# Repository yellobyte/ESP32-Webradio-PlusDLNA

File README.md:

# ESP32 Webradio++

This ESP32 internet radio implementation is partially based on Ed Smallenburgs (ed@smallenburg.nl) original ESP32 Radio project, version 10.06.2018. His active & very popular web radio project is documented [here](https://github.com/Edzelf/ESP32-radio).  

It all started when my much loved 1991's FM Tuner device **TECHNICS Tuner ST-G570** became obsolete and useless (at least for me). I simply couldn't listen to my favourite FM radio stations anymore after having moved abroad. Since I didn't want to part with the old longtime pal, the decision was made to give it a second life: housing a modern internet radio with lots of additional features.  

Now, after putting countless hours into the project, the device not only plays **internet radio streams** and audio files from **SD cards** but also **audio content from DLNA media servers** in the same LAN.  

The Arduino library **SoapESP32** has been created especially for the latter feature and enables any ESP32 based device to connect to DLNA media servers in the local network, browse their content and download selected files. It is basically a byproduct of this project and is now listed in the official Arduino library [collection](https://www.arduino.cc/reference/en/libraries/category/communication/).  

## :gift: Feature list:

Starting from Ed Smallenburg's code (Version 10.06.2018) this project has seen a lot of additions and modifications over time. Here a summary:

 * Integration of [SoapESP32](https://github.com/yellobyte/SoapESP32) library for DLNA media server access
 * Digital audio output added (TOSLINK optical) using a WM8805 module from Aliexpress
 * Usage of special VS1053 decoder board (with I2S output and without 3.5mm audio socket)<br />
   -> You find the Eagle schematic & board files [here](https://github.com/yellobyte/ESP32-Webradio-PlusDLNA/tree/main/EagleFiles).
 * VS1053 gets patched with new firmware v2.7 at each reboot<br />
   -> Latest firmware patches for the VLSI VS1053 are available from [here](http://www.vlsi.fi/en/support/software/vs10xxpatches.html).
 * VU meter added to TFT display (needs above mentioned firmware patch)
 * Usage of W5500 Ethernet module instead of ESP32 builtin WiFi
 * Option to use a Debug Server on port 23 for debug output (in this case the cmd server is disabled due to Ethernet socket shortage)
 * Handling of the original front panel buttons & LEDs with the aid of an extender module (connected to ESP32 via I2C)
 * SD card indexing code rewritten in large parts
 * Ability to update ESP32 Radio code via SD card (using OTA functionality during reboot)
 * New rotary encoder fitted to available rotary knob, debouncing done in hardware
 * Track progress bar while playing audio files from SD card or media server
 * Minor modifications to get an unspecified Ali 21-button remote control working
 * MQTT functionality & battery stuff removed completely
 * Handling of more special chars in webradio streams (some radio channels seem to have different utf8 conversion tables)
 * Quicker handling of (very rare) firmware crashes resulting in shorter recovery/reboot time
 * Countless minor changes, adjustments, bugfixing
 * Regular modifications if required for building with new espressif32 framework releases   

If interested, have a look at [Revision history.txt](https://github.com/yellobyte/ESP32-Webradio-PlusDLNA/blob/main/Doc/Revision%20history.txt) in the doc folder. 

## Some technical details:
The original display (rendered useless) has been removed and it's plexiglass cover now hides the infrared sensor VS1838B which receives signals from a remote control. A small 1.8" TFT color display (160x128 pixel, ST7735 driver IC, PCI bus) has been added to the front and is used for interacting with the user and presenting essential info. The necessary cutout in the front has been made with a small and affordable Proxxon mill/drill unit used by many hobbyists. A thin plexiglass is glued into the cutout. The TFT display sits right behind it, mounted on a frame made from PCB material to keep it in place. 

After milling/drilling the front was thoroughly cleaned to get a smooth surface and then the upper flat part of it was painted black twice with a bottle of color spray. It rested 3 days in the sun to dry completely before being reattached to the case. A silver permanent marker was used to label the buttons later on.  

The original encoder attached to the rotary knob has been replaced with a modern one (Stec Rotary Encoder STEC11B03, 1 impulse per 2 clicks, turn + push). The knob is now used to browse through the list of pre-configured web radio stations, the content of SD cards or DLNA media servers storing thousands of audio files. Going up and down the directory levels and finally selecting an audio file for playing is done very fast with the knob in combination with the small 'return' button next to it.  

Most of the original front buttons are still available and used for changing modes (Radio, SD card or DLNA), skipping tracks and selecting a repeat mode (None, Track, List or Random). Two adjacent buttons just below the TFT display went into the bin and made room for a SD card module (PCI bus with 4MHz clock speed only for stability reasons).   

A special extender board connects the mainboard with the original front PCB. This board makes it possible to control LEDs and buttons via the original control matrix. The existing 10 channel buttons (1...8,9,0) can continue to serve their original purpose, only this time with web radio stations assigned. The infrared sensor is attached to the extender board as well. 

The extender board contains two 'Remote 8-Bit I/O Expander for I2C Bus ICs' PCF8574 and is connected to the mainboard via I2C bus. Its only task is to provide additional IO ports to the ESP32 on the mainboard. Jumper JP1 on the board is open as the interrupt signal INT from both ICs is unused. Every ~60ms the ICs get polled from the ESP32 instead.

The original front panel 7x4 control matrix has all buttons connected between 7 rows and 4 columns as shown below. Quite a few single header pins had to be soldered onto the front panel PCB to get electrical access to the matrix. 

Rows 1...7 of the matrix (from top to bottom) are wired to connectors SV1 and SV2 on the extender board as follows:  
 * Row 1 (CP103/5) --> SV1/5 (PCF8574-1/P4, output)
 * Row 2 (CP103/4) is unused (buttons 'Preset up/down' have been removed)
 * Row 3 (CP102/8) --> SV2/2 (PCF8574-2/P1, output)
 * Row 4 (CP102/9) --> SV2/1 (PCF8574-2/P0, output)
 * Row 5 (CP103/6) --> SV1/6 (PCF8574-1/P5, output)
 * Row 6 (CP103/7) --> SV1/7 (PCF8574-1/P6, output)
 * Row 7 (CP103/8) --> SV1/8 (PCF8574-1/P7, output)

And colums 1...4 (from left to right) are wired to the extender board as follows:  
 * Column 1 (CP103/1) --> SV1/1 (PCF8574-1/P0, input, with 8.2k pull-up resistor to 3V3)
 * Column 2 (CP103/2) --> SV1/2 (PCF8574-1/P1, input, with 8.2k pull-up resistor to 3V3)
 * Column 3 (CP103/3) --> SV1/3 (PCF8574-1/P2, input, with 8.2k pull-up resistor to 3V3)
 * Column 4 (CP102/7) --> SV1/4 (PCF8574-1/P3, input, with 8.2k pull-up resistor to 3V3)

In order to detect pressed buttons the extender board successively pulls the rows LOW and checks it's column input lines for a HIGH to LOW transition because any button pressed will then subsequently pull its corresponding column to LOW as well.

The extender board additionally drives the 3 front panel LEDs via IC PCF8574-2/P5-P7 (connector pins SV2/6...8) by setting the lines to LOW. Those 3 lines plus 3V3 are wired directly to a separate LED PCB next to the rotary encoder.  

As for now, the device consists of several separate modules/PCBs. Three modules (ESP32, TOSLINK optical output, 10/100Mb Ethernet) were bought from various internet shops and the other four modules (power supply, mainboard, VS1053B decoder and front extender) were especially designed for this project with EAGLE PCB Design & Layout tool. The PCBs were ordered unassembled from various PCB prototype manufacturers in CN for little money. I did all the soldering myself, the decoder chip VS1053B in a tiny LQFP-48 package was a challenge though. All relevant EAGLE project files, schematics, board layouts etc. are available [here](https://github.com/yellobyte/ESP32-Webradio-PlusDLNA/tree/main/EagleFiles).  

The analog audio output socket, the power input socket, the common mode choke and the many PCB distance holders were harvested from the original tuner PCBs and reused. Their Eagle-Libraries are located [here](https://github.com/yellobyte/Eagle-Component-Library). The mounting holes on the new PCBs were placed in a way to match the existing mounting holes at the bottom of the case.  

A necessary audio amplifier can be connected via the analog audio output or even the TOSLINK optical output for better sound quality. Well, going digital at the output is probably useless for web radio stations only, as their stream bit rates mostly range between 32...128kbps and very rarely top 192kbps.  

The special VS1053B decoder module (the red one in the middle) provides an I2S output which connects the decoder with the TOSLINK optical output module (the green one on the left). Since all available VS1053B decoder modules on Ali etc. lacked an I2S port I unavoidably had to build my own one. 

If a digital audio output is not needed than any of the available cheap VS1053B decoder modules with 3.5mm jack socket (and without I2S socket) would do.  

The WM8805 I2S to TOSLINK module (China) was the cheapest module version I could get as it lacks the COAX output socket, the crystal oscillator, some Cs, Rs and the power input socket. However, all this is not needed in this project. Important was the ability to configure the WM8805 simply with Rs on the module and the presence of a TOSLINK output socket. 

The WM8805 can be operated in either software or hardware control mode. The mode is determined by sampling the state of the SDIN pin. If SDIN is LOW
during power up or hardware reset then the WM8805 switches into hardware control mode. In this mode most features will assume default values but some can be configured using external pins (SDOUT, SCLK, CSB, GPO0). 

Having the respective Rs soldered as shown below gives the following configuration of the chip: hardware control mode (SDIN=LOW), slave mode (SCLK=LOW), S/PDIF transmitter data source is I2S (CSB=HIGH) and the I2S interface expects 16-bit data (GPO0=LOW, SDOUT=LOW).  

To make the optical output work the decoder chip VS1053B is programmed to feed the WM8805 with 12.288MHz MCLK, 48kHz LRCK (MCLK divided by 256) and 16-bit audio data as configured.

The controller board used on the mainboard is an inexpensive ESP32-T dev board equipped with an ESP32-Bit module (4MB Flash, 512kB RAM, no PSRAM, ultra small SMD WLAN antenna, I-PEX WLAN socket). Compared with other popular ESP32 dev boards the ESP32-T is slimmer and therefore even more breadboard compatible. I used it in the first flying test set and since it worked without issues I decided to keep it in the final project.

For my next similar project (this time an old Denon TU-550 tuner case from the early 90's) I will use the [YB-ESP32-S3-ETH dev board](https://github.com/yellobyte/YB-ESP32-S3-ETH) as it combines ESP32 + Ethernet + Wifi + debug port on a single small dev board. Both versions -N4 and -N8R8 will do but the latter provides 8MB PSRAM which allows buffering audio streams if that was needed. This board will allow to make the main board much smaller as well.

During the early stages of the project a lot of software updates were required and all were done via USB cable between ESP32-module and PC. However, at some stage the device rejoined the HiFi rack and opening the case now and then for a quick software update became a real pain in the butt. Hence the possibility to perform an ESP32 firmware update simply via SD card was added.  

Plenty of holes were drilled at the back of the case for better thermal management but they later proved unnecessary as the temps inside the case always stayed below 35 degs even with the lid on and all holes covered.  

If Ethernet is not wanted/possible than a small WLAN antenna attached with a short cable to the ESP32 WLAN-socket (I-PEX) would suffice. In that case I recommend to place the antenna directly behind the plexiglass cover for better receiption. Early tests with a WLAN router in 3m distance and fully closed case showed no issues with that arrangement.  

## Hardware troubleshooting:

In the early stages of the project the device was sometimes not able to establish an Ethernet connection after being switched on and it took me quite a while to figure out the problem. As it turned out, the W5500 Ethernet chip needs to be resetted substantially longer after power on than e.g the ESP32 chip.  Hence I modified the mainboard and replaced the original RC combination holding the reset line low with a Microchip MCP130T-315. This is a voltage supervisory IC designed to keep a microcontroller or any other chip in reset for a determined time (typically 350ms) after the system voltage has reached the desired level (here >= 3.15V) and stabilized. With that chip the connection issue vanished for good. 

Another troubling issue were the infrequent system resets after inserting a SD card into the SD card socket while the system was running. I figured it might be the MISO signal from the SD card module being directly attached to the ESP32. After adding driver gates IC2B (HC4050) and IC3D (74HC125) into the path between ESP32 and SD module this problem was gone as well. This solution disconnects the SD modules's MISO signal from the system and therefor prevents any interference from the SD card module when its assigned chip select signal SDCS is inactive (high). 

Since mechanical rotary encoders (independent of their build quality) need to be debounced I decided very early in the project to perform it fully in hardware by using RC circuits (10k/100n) in combination with Schmitt-Trigger ICs (74HC14).  As expected, debouncing issues never surfaced and no line of code had to be wasted on this topic.  

As visible in the main board schematic above, the inputs of all unused 74HC gates are kept grounded and not floating in order to avoid possible gate oscillation as their inputs are all high impedance (in contrast to e.g. old 7400's). Furthermore I added plenty of capacitors near the ICs and close to each socket, connector etc. in order to keep the power supply rail as clean as possible.

## :zap: Software application notes:

All coding was done with **VSCode/PlatformIO-IDE**. To install needed libraries (Ethernet, SoapESP32, etc.) click the **PlatformIO sidebar icon**, open the **libraries** view and search for libs. Once found, select the newest release and click on **Add to Project**.

Always make sure you have one of the latest versions of the **Arduino ESP32 framework** installed. Older versions might produce build errors. Actual build (Aug 2026) was successfully done with Espressif's latest Arduino ESP32 framework V3.3.11. Have a look at file [platformio.ini](https://github.com/yellobyte/ESP32-Webradio-PlusDLNA/blob/main/Software/platformio.ini) for required settings and logfile [Build.log](https://github.com/yellobyte/ESP32-Webradio-PlusDLNA/blob/main/Software/Build.log).

## :tada: Implementation of SoapESP32 library for DLNA server access

The lib makes retrieving audio files from a DLNA media server a breeze: Function *browseServer()* is used to scan the server content and return a list of tracks (audio files). The device then selects an item from the list and sends a read request to the media server using *readStart()*. If granted, it will repeatedly *read()* a chunk of data into the queue which feeds the audio codec VS1053B until end of file. Finally the data connection to the server is closed with *readStop()* and the next item from the list is requested, provided the 'repeat file/folder' mode is active.  

The following sample picture sequence shows the actual implementation into this webradio project:

Alternatively have a look at the short clip _ESP32-Radio-DLNA.mp4_ in folder **Doc** to see the final implementation in action. To watch now, click [Here](https://github.com/yellobyte/ESP32-Webradio-PlusDLNA/blob/main/Doc/ESP32-Radio-DLNA.mp4).

## :hammer_and_wrench: Still to be done:

 * Enable the Webinterface to browse DLNA media servers and select audio files for playing.

## :relaxed: Postscript:

Maybe this project can inspire one or two owners of old HiFi equipment to give their devices a second chance instead of tossing them into the scrap metal container. I spent a lot of time and efforts doing this project and wouldn't want to miss a second of it for I had plenty of fun and learned many things as well.  

If you have questions, miss some information or have suggestions, feel free to create an issue or contact me. However, my response time might be slow at times.

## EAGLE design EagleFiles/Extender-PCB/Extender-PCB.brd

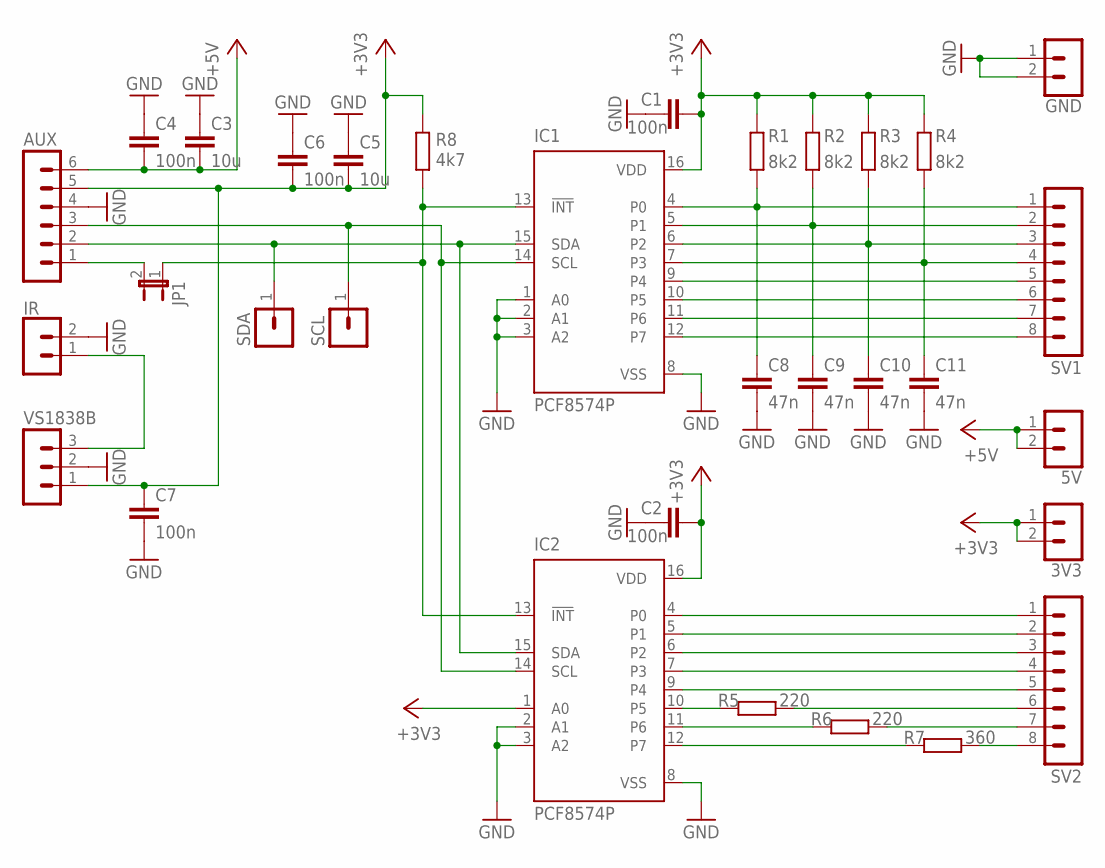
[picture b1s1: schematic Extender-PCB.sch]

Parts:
3V3, 5V: MA02-1
AUX: MA06-1
C1, C2, C4, C6, C7: 100n; C1206
C3, C5: 10u; C1206
C8, C9, C10, C11: 47n; C1206
GND: MA02-1
IC1, IC2: PCF8574P; DIL16
IR: MA02-1
JP1: JP1E; JP1
R1, R2, R3, R4: 8k2; R1206
R5, R6: 220; 0207/10
R7: 360; 0207/10
R8: 4k7; 0207/10
SCL: MA01-1
SDA: MA01-1
SV1, SV2: MA08-1
VS1838B: MA03-1

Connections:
+3V3: 3V3.1, 3V3.2, AUX.5, C1.2, C2.2, C5.2, C6.2, C7.1, IC1.16 (VDD), IC2.1 (A0), IC2.16 (VDD), R1.2, R2.2, R3.2, R4.2, R8.2, VS1838B.1
+5V: 5V.1, 5V.2, AUX.6, C3.2, C4.2
GND: AUX.4, C1.1, C2.1, C3.1, C4.1, C5.1, C6.1, C7.2, C8.2, C9.2, C10.2, C11.2, GND.1, GND.2, IC1.1 (A0), IC1.2 (A1), IC1.3 (A2), IC1.8 (VSS), IC2.2 (A1), IC2.3 (A2), IC2.8 (VSS), IR.2, VS1838B.2
LED1: R5.2, SV2.6
LED2: R6.2, SV2.7
LED3: R7.2, SV2.8
unnamed: AUX.1, JP1.2
unnamed: IC1.13 (!INT), IC2.13 (!INT), JP1.1, R8.1
unnamed: IR.1, VS1838B.3
P0-1: C8.1, IC1.4 (P0), R1.1, SV1.1
P0-2: IC2.4 (P0), SV2.1
P1-1: C9.1, IC1.5 (P1), R2.1, SV1.2
P1-2: IC2.5 (P1), SV2.2
P2-1: C10.1, IC1.6 (P2), R3.1, SV1.3
P2-2: IC2.6 (P2), SV2.3
P3-1: C11.1, IC1.7 (P3), R4.1, SV1.4
P3-2: IC2.7 (P3), SV2.4
P4-1: IC1.9 (P4), SV1.5
P4-2: IC2.9 (P4), SV2.5
P5-1: IC1.10 (P5), SV1.6
P5-2: IC2.10 (P5), R5.1
P6-1: IC1.11 (P6), SV1.7
P6-2: IC2.11 (P6), R6.1
P7-1: IC1.12 (P7), SV1.8
P7-2: IC2.12 (P7), R7.1
SCL: AUX.3, IC1.14 (SCL), IC2.14 (SCL), SCL.1
SDA: AUX.2, IC1.15 (SDA), IC2.15 (SDA), SDA.1

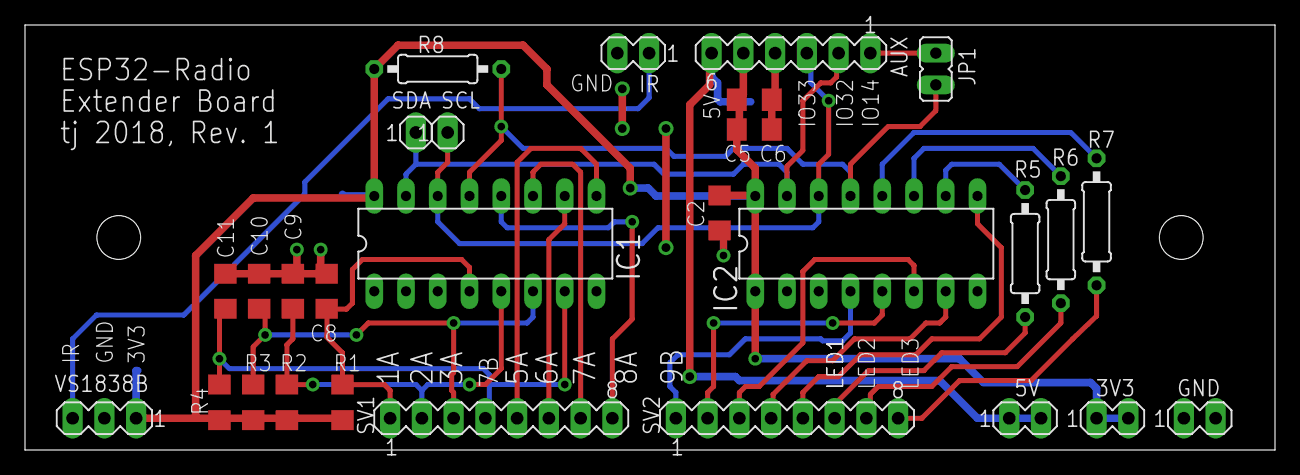
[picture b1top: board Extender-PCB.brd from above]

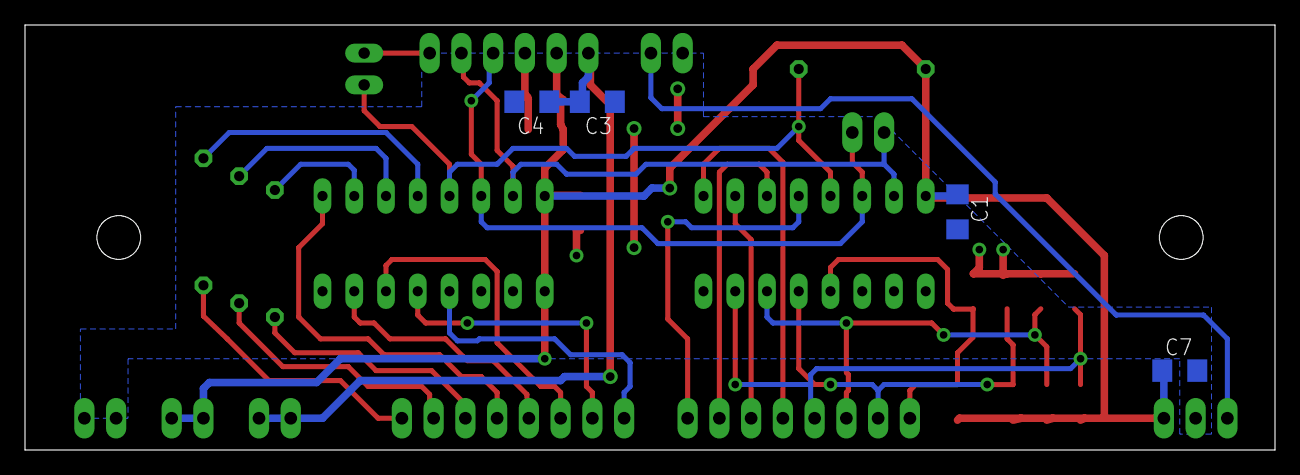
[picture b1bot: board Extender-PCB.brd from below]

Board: 2 copper layers, 100.0 x 34.0 mm, 32 parts (4 on the bottom side), 27 nets.

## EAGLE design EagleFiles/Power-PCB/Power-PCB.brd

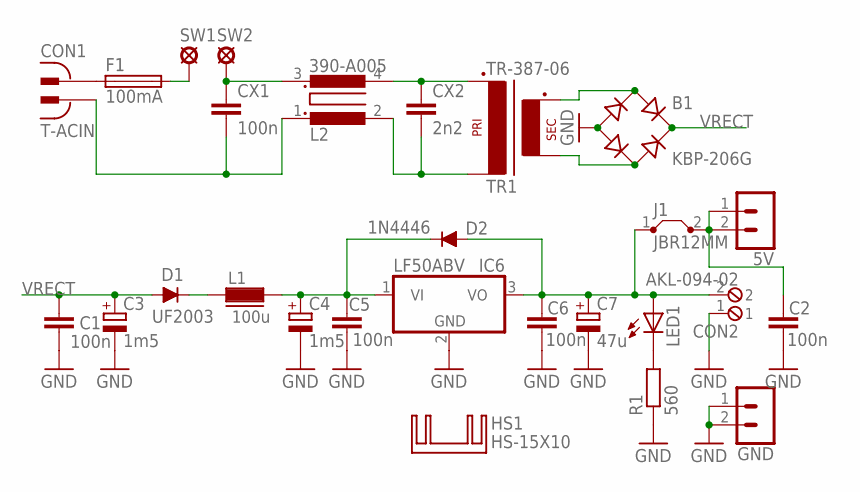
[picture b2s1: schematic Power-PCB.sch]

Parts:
5V: MA02-1
B1: KBP-206G; 2KBP
C1, C2, C5, C6: 100n; C050-024X044
C3, C4: 1m5; E5-10,5
C7: 47u; E2,5-6
CON1: T-ACIN; TECHNICS-ACIN1
CON2: AKL-094-02
CX1: 100n; XC15B6
CX2: 2n2; C075-032X103
D1: UF2003; DO41-10A
D2: 1N4446; DO35-10
F1: 100mA; KS9V
GND: MA02-1
HS1: HS-15X10; HEATSINK-TO220-15X10X21
IC6: LF50ABV; TO220V
J1: JBR12MM; 12-THICK-WIRE
L1: 100u; 07HCP
L2: 390-A005
LED1: LED5MM
R1: 560; 0207/10
SW1, SW2: SE13
TR1: TR-387-06; TRAFO-GERTH-387-06

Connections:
GND: B1.-, C1.2, C2.2, C3.-, C4.-, C5.2, C6.2, C7.-, CON2.1, GND.1, GND.2, IC6.2 (GND), R1.1
unnamed: CON1.1, F1.1
unnamed: CX1.1, L2.3, SW2.MP
unnamed: CON1.2, CX1.2, L2.1
unnamed: F1.2, SW1.MP
unnamed: C4.+, C5.1, D2.C, IC6.1 (VI), L1.2
unnamed: CX2.1, L2.4, TR1.P2
unnamed: CX2.2, L2.2, TR1.P1
unnamed: B1.AC1, TR1.S2
unnamed: B1.AC2, TR1.S1
unnamed: LED1.K (C), R1.2
unnamed: D1.C, L1.1
unnamed: C6.1, C7.+, CON2.2, D2.A, IC6.3 (VO), J1.1, LED1.A
unnamed: 5V.1, 5V.2, C2.1, J1.2
VRECT: B1.+, C1.1, C3.+, D1.A

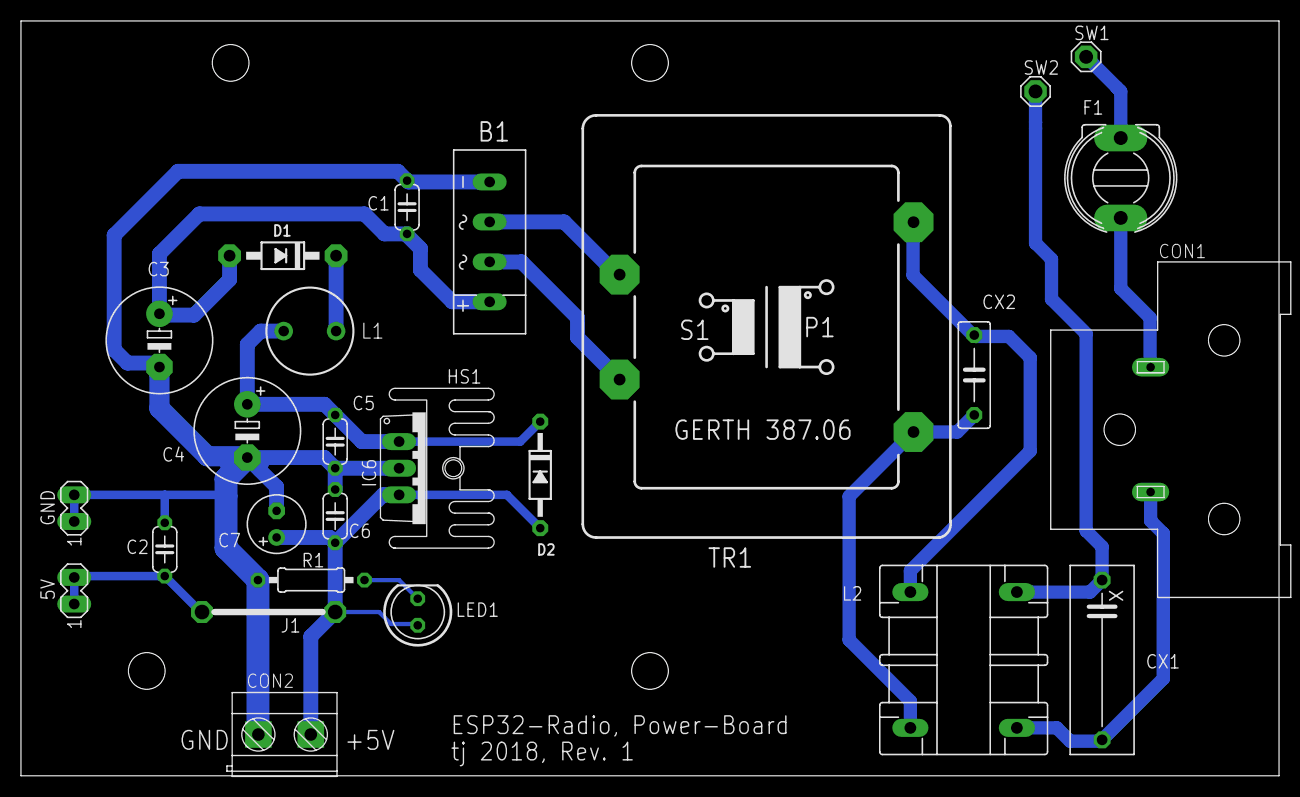
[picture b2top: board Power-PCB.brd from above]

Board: 2 copper layers, 120.0 x 72.0 mm, 27 parts (0 on the bottom side), 15 nets.

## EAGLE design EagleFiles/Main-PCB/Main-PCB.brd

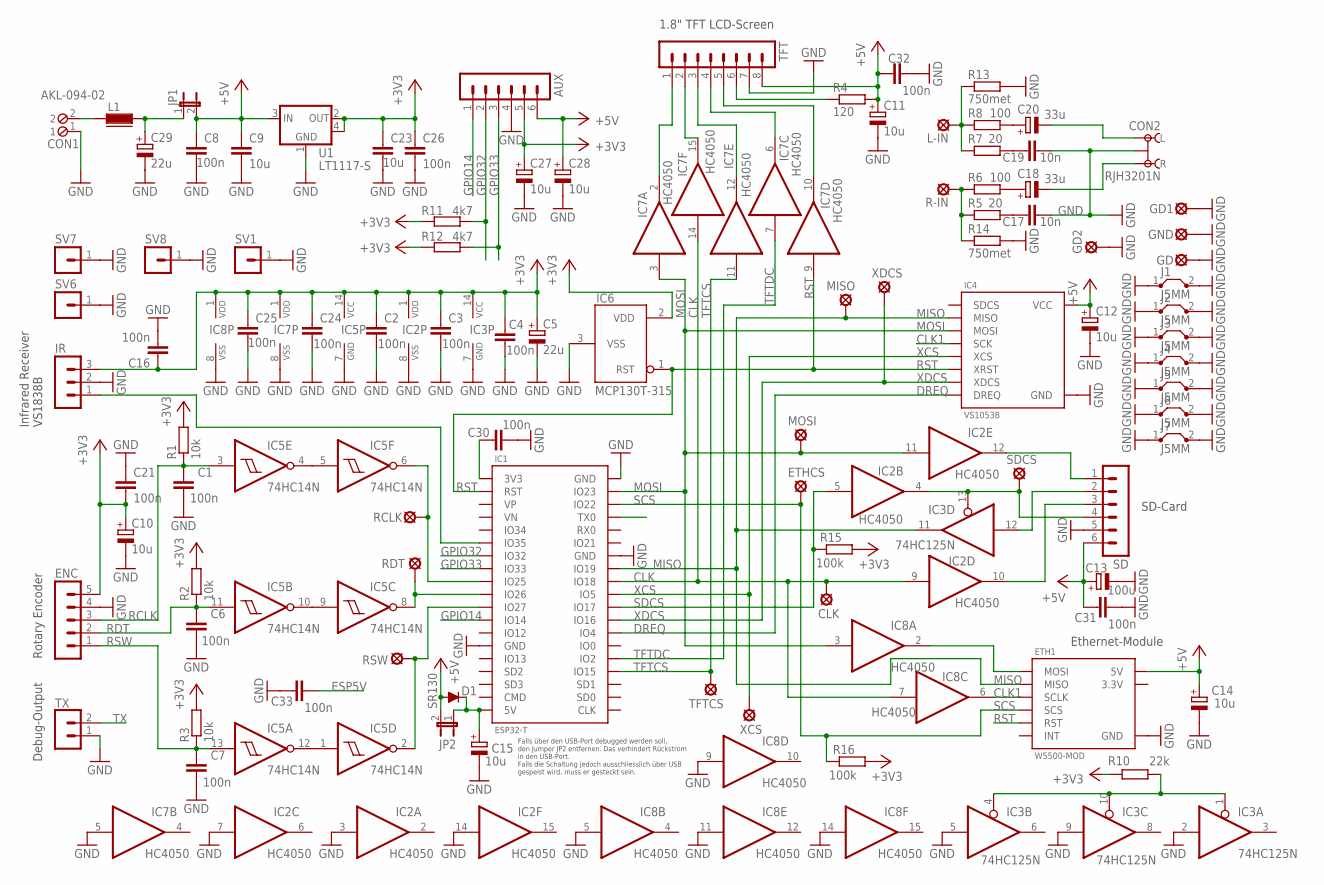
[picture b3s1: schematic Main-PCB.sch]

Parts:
AUX: MA06-1
C1, C6, C7: 100n; C050-024X044
C2, C3, C4, C8, C16, C21, C24, C25, C26, C30, C31, C32, C33: 100n; C1206
C5, C29: 22u; TT2D4
C9, C23: 10u; C1206
C10, C11, C14, C15, C27, C28: 10u; TT2D4
C12: 10u; TT2D4L
C13: 100u; E2,5-6
C17, C19: 10n; C1206
C18, C20: 33u; TT2D4
CLK: LSP11
CON1: AKL-094-02
CON2: RJH3201N; TECHNICS-RJH3201N
D1: SR130; D-7.5
ENC: MA05-1
ETH1: W5500-MOD
ETHCS: LSP11
GD, GD1: LSP11
GD2: SE13
GND: LSP11
IC1: ESP32-T
IC2, IC7, IC8: HC4050; DIL16
IC3: 74HC125N; DIL14
IC4: VS1053B
IC5: 74HC14N; DIL14
IC6: MCP130T-315; SOT-23
IR: MA03-1
J1, J2, J3, J4, J5, J6, J7: J5MM; 05
JP1, JP2: JP1E; JP1
L1: 07HCP
L-IN: LSP11
MISO: LSP11
MOSI: LSP11
R1, R2, R3: 10k; 0207/10
R4: 120; 0207/10
R5, R7: 20; R1206
R6, R8: 100; R1206
R10: 22k; R1206
R11, R12: 4k7; R1206
R13, R14: 750met; 0207/10
R15, R16: 100k; R1206
R-IN: LSP11
RCLK: LSP11
RDT: LSP11
RSW: LSP11
SD: MA06-1
SDCS: LSP11
SV1, SV6, SV7, SV8: MA01-1
TFT: MA08-1
TFTCS: LSP11
TX: MA02-1
U1: LT1117-S; SOT223
XCS: LSP11
XDCS: LSP11

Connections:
3.3V: ETH1.3.3V
+3V3: AUX.5, C2.1, C3.1, C4.1, C5.+, C10.+, C16.1, C21.2, C23.1, C24.1, C25.1, C26.1, C27.+, ENC.5, IC2.1 (VDD), IC3.14 (VCC), IC5.14 (VCC), IC6.2 (VDD), IC7.1 (VDD), IC8.1 (VDD), IR.3, R1.2, R2.2, R3.2, R10.1, R11.2, R12.2, R15.2, R16.2, U1.2 (OUT), U1.4 (TAB)
+5V: AUX.6, C8.1, C9.1, C11.+, C12.+, C13.+, C14.+, C28.+, C31.2, C32.2, D1.A, ETH1.5V, IC4.5V (VCC), JP1.2, JP2.2, R4.2, SD.6, TFT.8, U1.3 (IN)
CLK: CLK.MP, IC1.IO18, IC2.9 (I), IC7.14 (I), IC8.7 (I)
CLK1: ETH1.SCLK, IC4.SCK, IC8.6 (O)
DREQ: IC1.IO4, IC4.DREQ
ESP5V: C15.+, C33.1, D1.C, IC1.5V, JP2.1
ETHMOSI: ETH1.MOSI, IC8.2 (O)
GND: AUX.4, C1.2, C2.2, C3.2, C4.2, C5.-, C6.2, C7.2, C8.2, C9.2, C10.-, C11.-, C12.-, C13.-, C14.-, C15.-, C16.2, C17.2, C19.2, C21.1, C23.2, C24.2, C25.2, C26.2, C27.-, C28.-, C29.-, C30.2, C31.1, C32.1, C33.2, CON1.1, CON2.GND, ENC.4, ETH1.GND, GD.MP, GD1.MP, GD2.MP, GND.MP, IC1.GND, IC1.GND1 (GND), IC1.GND2 (GND), IC2.3 (I), IC2.7 (I), IC2.8 (VSS), IC2.14 (I), IC3.2 (I), IC3.5 (I), IC3.7 (GND), IC3.9 (I), IC4.GND, IC5.7 (GND), IC6.3 (VSS), IC7.5 (I), IC7.8 (VSS), IC8.5 (I), IC8.8 (VSS), IC8.9 (I), IC8.11 (I), IC8.14 (I), IR.2, J1.1, J1.2, J2.1, J2.2, J3.1, J3.2, J4.1, J4.2, J5.1, J5.2, J6.1, J6.2, J7.1, J7.2, R13.2, R14.2, SD.5, SV1.1, SV6.1, SV7.1, SV8.1, TFT.7, TX.1, U1.1 (GND)
GPIO14: AUX.1, IC1.IO14
GPIO32: AUX.2, IC1.IO32, R11.1
GPIO33: AUX.3, IC1.IO33, R12.1
IR: IC1.IO35, IR.1
MISO: ETH1.MISO, IC1.IO19, IC3.11 (O), IC4.MISO, MISO.MP
MOSI: IC1.IO23, IC2.11 (I), IC4.MOSI, IC7.3 (I), IC8.3 (I), MOSI.MP
unnamed: IC5.1 (I), IC5.12 (O)
unnamed: IC5.4 (O), IC5.5 (I)
unnamed: IC5.9 (I), IC5.10 (O)
unnamed: R4.1, TFT.6
unnamed: CON1.2, L1.1
unnamed: IC1.IO25, IC5.6 (O), RCLK.MP
unnamed: IC1.IO26, IC5.8 (O), RDT.MP
unnamed: C29.+, JP1.1, L1.2
unnamed: IC1.IO27, IC5.2 (O), RSW.MP
unnamed: C30.1, IC1.3V3
unnamed: R5.1, R6.1, R14.1, R-IN.MP
unnamed: C17.1, R5.2
unnamed: C18.+, R6.2
unnamed: C18.-, CON2.R
unnamed: L-IN.MP, R7.1, R8.1, R13.1
unnamed: C19.1, R7.2
unnamed: C20.+, R8.2
unnamed: C20.-, CON2.L
unnamed: IC3.1 (OE), IC3.4 (OE), IC3.10 (OE), R10.2
RCLK: C1.1, ENC.3, IC5.3 (I), R1.1
RDT: C6.1, ENC.2, IC5.11 (I), R2.1
RST: ETH1.RST, IC1.RST, IC4.XRST, IC6.1 (RST), IC7.9 (I)
RSW: C7.1, ENC.1, IC5.13 (I), R3.1
SCS: ETH1.SCS, ETHCS.MP, IC1.IO22, R16.1
SDCLK: IC2.10 (O), SD.3
SDCS: IC1.IO17, IC2.5 (I), R15.1
SDCS1: IC2.4 (O), IC3.13 (OE), SD.4, SDCS.MP
SDMISO: IC3.12 (I), SD.2
SDMOSI: IC2.12 (O), SD.1
TFTCLK: IC7.15 (O), TFT.2
TFTCS: IC1.IO15, IC7.11 (I), TFTCS.MP
TFTCS1: IC7.12 (O), TFT.3
TFTDC: IC1.IO2, IC7.7 (I)
TFTDC1: IC7.6 (O), TFT.4
TFTMOSI: IC7.2 (O), TFT.1
TFTRST: IC7.10 (O), TFT.5
TX: IC1.TX0, TX.2
XCS: IC1.IO5, IC4.XCS, XCS.MP
XDCS: IC1.IO16, IC4.XDCS, XDCS.MP

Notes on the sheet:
1.8" TFT LCD-Screen
SD-Card
Ethernet-Module
Rotary Encoder
Infrared Receiver VS1838B
Falls über den USB-Port debugged werden soll, den Jumper JP2 entfernen. Das verhindert Rückstrom in den USB-Port. Falls die Schaltung jedoch ausschliesslich über USB gespeist wird, muss er gesteckt sein.
Debug-Output

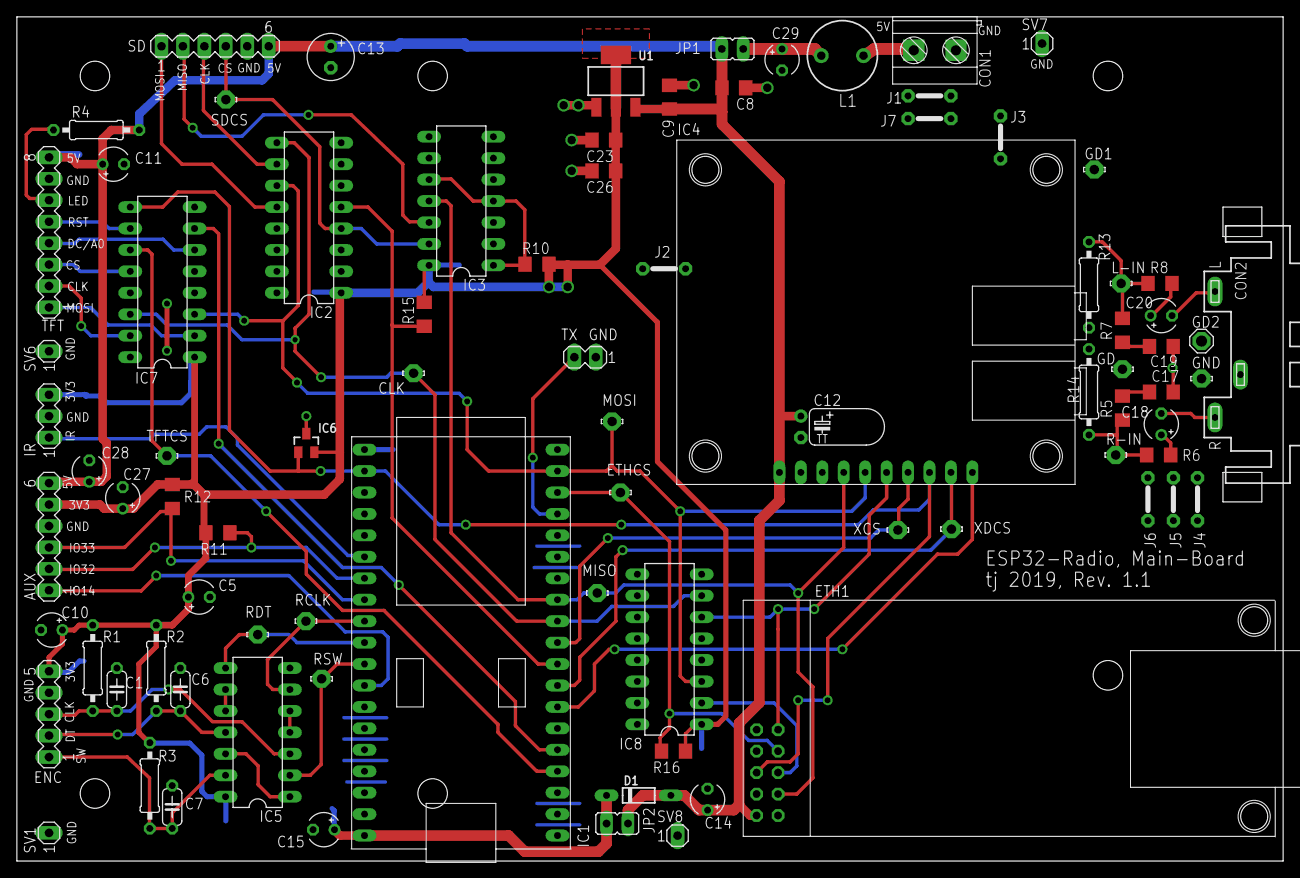
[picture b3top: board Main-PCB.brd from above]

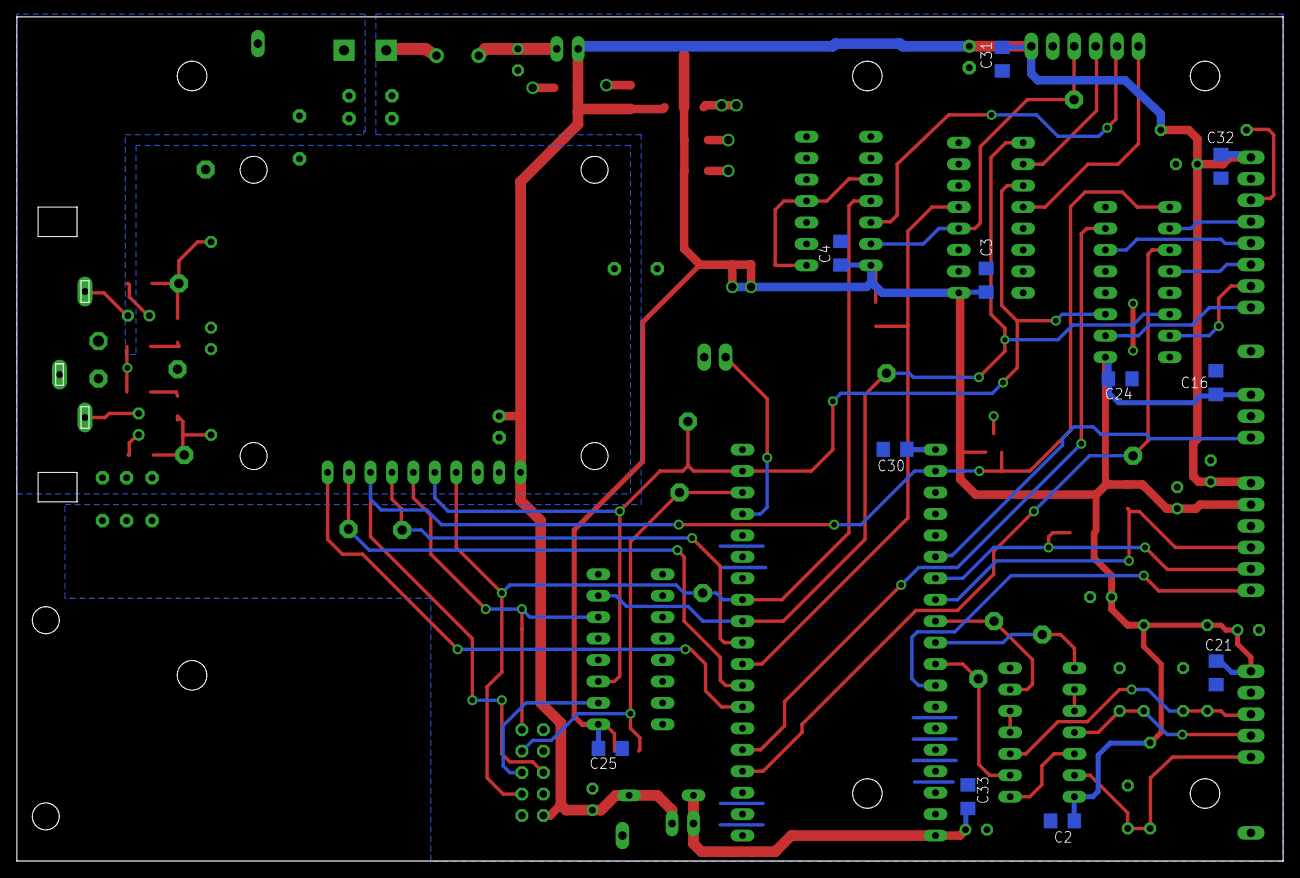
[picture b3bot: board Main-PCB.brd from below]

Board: 2 copper layers, 150.0 x 100.0 mm, 97 parts (11 on the bottom side), 53 nets.

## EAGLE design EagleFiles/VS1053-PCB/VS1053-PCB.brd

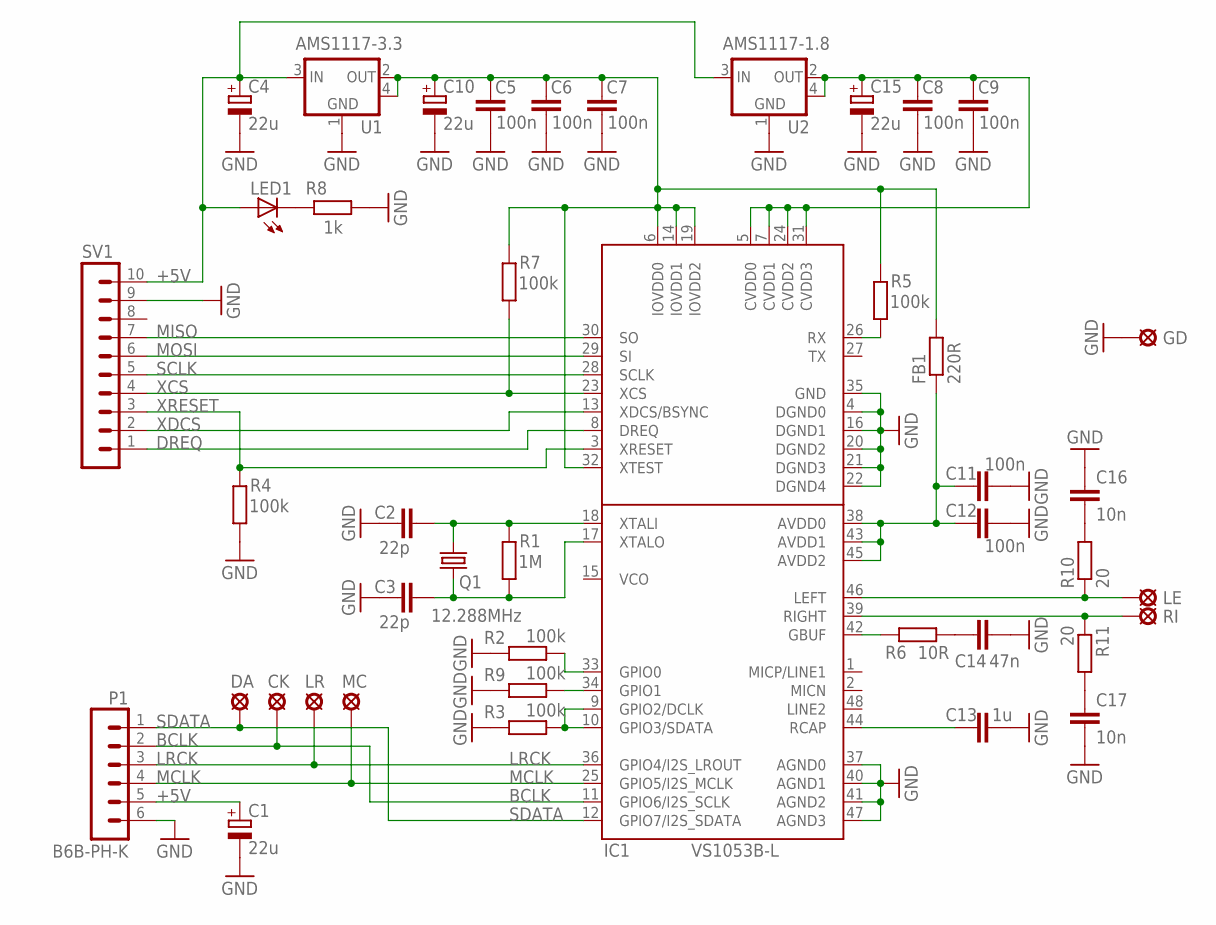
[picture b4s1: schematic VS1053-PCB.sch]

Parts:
C1, C4, C10, C15: 22u; CT3528
C2, C3: 22p; C0805
C5, C6, C7, C8, C9, C11, C12: 100n; C0805
C13: 1u; C0805
C14: 47n; C0805
C16, C17: 10n; C0603
CK: SOLPAD-MINI
DA: SOLPAD-MINI
FB1: 220R; R0805
GD: LSP10-ROUND
IC1: VS1053B-L; QFP50P900X900X160-48N
LE: LSP10-ROUND
LED1: LEDCHIPLED_0805; CHIPLED_0805
LR: SOLPAD-MINI
MC: SOLPAD-MINI
P1: B6B-PH-K
Q1: 12.288MHz; HC49/S
R1: 1M; R0805
R2, R3, R4, R5, R7, R9: 100k; R0805
R6: 10R; R0805
R8: 1k; R0805
R10, R11: 20; R0603
RI: LSP10-ROUND
SV1: MA10-1-THIN
U1: AMS1117-3.3; SOT223
U2: AMS1117-1.8; SOT223

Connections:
3.3VA: C11.1, C12.1, FB1.1, IC1.38 (AVDD0), IC1.43 (AVDD1), IC1.45 (AVDD2)
+1.8V: C8.1, C9.1, C15.+, IC1.5 (CVDD0), IC1.7 (CVDD1), IC1.24 (CVDD2), IC1.31 (CVDD3), U2.2 (OUT), U2.4 (TAB)
+3.3V: C5.1, C6.1, C7.1, C10.+, FB1.2, IC1.6 (IOVDD0), IC1.14 (IOVDD1), IC1.19 (IOVDD2), IC1.32 (XTEST), R5.2, R7.2, U1.2 (OUT), U1.4 (TAB)
+5V: C1.+, C4.+, LED1.A, P1.5, SV1.10, U1.3 (IN), U2.3 (IN)
BCLK: CK.1, IC1.11 (GPIO6/I2S_SCLK), P1.2
DREQ: IC1.8 (DREQ), SV1.1
GND: C1.-, C2.1, C3.1, C4.-, C5.2, C6.2, C7.2, C8.2, C9.2, C10.-, C11.2, C12.2, C13.2, C14.2, C15.-, C16.1, C17.2, GD.MP, IC1.4 (DGND0), IC1.16 (DGND1), IC1.20 (DGND2), IC1.21 (DGND3), IC1.22 (DGND4), IC1.35 (GND), IC1.37 (AGND0), IC1.40 (AGND1), IC1.41 (AGND2), IC1.47 (AGND3), P1.6, R2.2, R3.2, R4.1, R8.2, R9.2, SV1.9, U1.1 (GND), U2.1 (GND)
LRCK: IC1.36 (GPIO4/I2S_LROUT), LR.1, P1.3
MCLK: IC1.25 (GPIO5/I2S_MCLK), MC.1, P1.4
MISO: IC1.30 (SO), SV1.7
MOSI: IC1.29 (SI), SV1.6
unnamed: C2.2, IC1.18 (XTALI), Q1.2, R1.2
unnamed: C3.2, IC1.17 (XTALO), Q1.1, R1.1
unnamed: IC1.9 (GPIO2/DCLK), IC1.10 (GPIO3/SDATA), R3.1
unnamed: IC1.33 (GPIO0), R2.1
unnamed: IC1.42 (GBUF), R6.1
unnamed: C13.1, IC1.44 (RCAP)
unnamed: C14.1, R6.2
unnamed: IC1.39 (RIGHT), R11.1, RI.MP
unnamed: IC1.26 (RX), R5.1
unnamed: IC1.46 (LEFT), LE.MP, R10.1
unnamed: IC1.34 (GPIO1), R9.1
unnamed: LED1.C, R8.1
unnamed: C16.2, R10.2
unnamed: C17.1, R11.2
SCLK: IC1.28 (SCLK), SV1.5
SDATA: DA.1, IC1.12 (GPIO7/I2S_SDATA), P1.1
XCS: IC1.23 (XCS), R7.1, SV1.4
XDCS: IC1.13 (XDCS/BSYNC), SV1.2
XRESET: IC1.3 (XRESET), R4.2, SV1.3

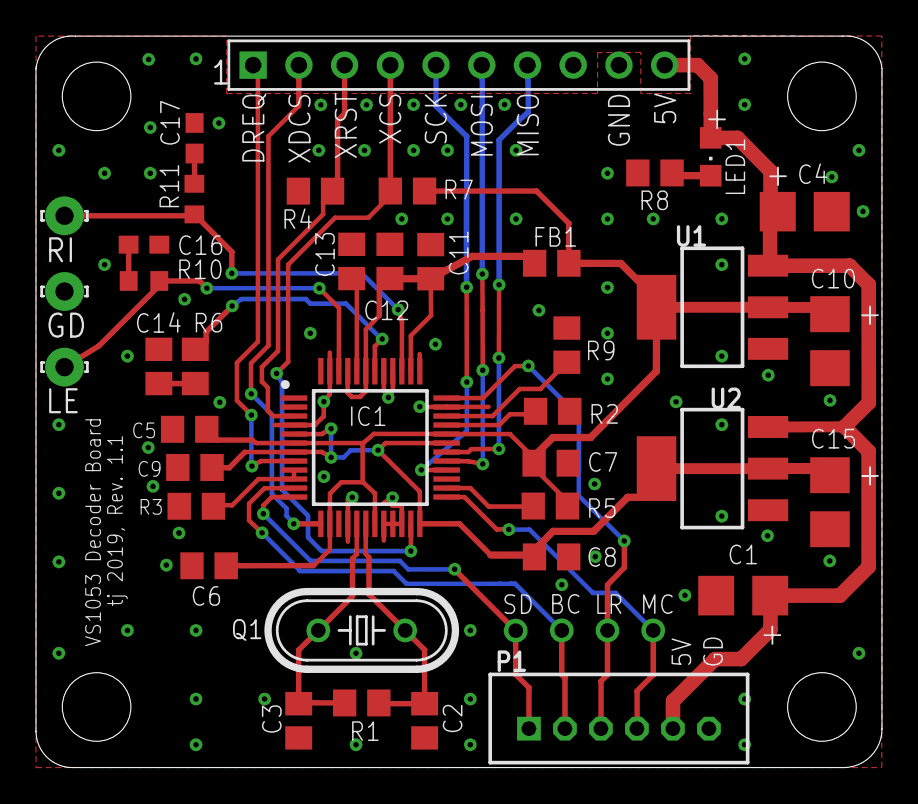
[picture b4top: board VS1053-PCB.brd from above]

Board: 2 copper layers, 47.0 x 40.6 mm, 43 parts (0 on the bottom side), 30 nets.

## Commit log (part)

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2021-04-13 First release
2021-04-13 Fixed links in Readme.md
2021-04-13 improved documentation
2021-04-13 picture resolution improved
2021-04-13 file deleted
2021-04-13 pic resolution changed
2021-10-11 Update main.cpp
    Better error handling when connection to station is lost.
2022-01-30 Minor changes in utf8ascii()
2022-02-02 Application notes added
2022-05-16 Update main.cpp
    Fix for latest Espressif 32 platform >= V4.0.0. Better error handling. Minor improvements.
2022-05-18 Minor fix to prevent build warning
    #ifdef directive fixed in main.cpp, line 381
2022-07-14 modification for espressif32 framework >= V4.2.0
    1) required modification for Arduino espressif32 framework >= V4.2.0
    (successful PlatformIO builds for V4.2.0 & V5.0.0)
    2) minor improvements
2022-07-15 displaying text improved
2023-10-10 doc improved
2023-10-10 new pic
2023-10-14 file name changed
2024-01-09 Comments corrected in section PCF8574
2024-01-09 Cosmetic changes
2024-01-10 Minor changes in showStreamTitle()
    Some radio stations send a streamtitle followed by an empty one. The second & empty one is now suppressed.
2024-01-11 unused variable removed, minor change in showStreamTitle()
